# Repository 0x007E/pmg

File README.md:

# `PMG` - Audio Level Meter (Pegelmessgerät)

The `pmg` project is based on a pcb with an elektret microphone signal transistor (`BC547`) amplifier and a transistor stage for level signalization.

| Experience | Level |
|:------------|:-----:|
| Soldering   |  |
| Mechanical  |  |

# Downloads

| Type      | File               | Description              |
|:---------:|:------------------:|:-------------------------|
| Simulation | [asc](https://github.com/0x007E/pmg/raw/refs/heads/main/PMG.asc) | LTSpice Simulation | 
| Lochmaster | [lm4](https://github.com/0x007E/pmg/raw/refs/heads/main/PMG.LM4) | Stripe grid circuit board | 
| Schematic | [pdf](https://github.com/0x007E/pmg/releases/latest/download/schematic.pdf) / [cadlab](https://cadlab.io/project/28569/main/files)     | Schematic files          |
| Board     | [pdf](https://github.com/0x007E/pmg/releases/latest/download/pcb.pdf) / [cadlab](https://cadlab.io/project/28569/main/files)     | Board file               |
| Drill     | [pdf](https://github.com/0x007E/pmg/releases/latest/download/drill.pdf) | Drill file               |
| BoM | [xlsx](https://github.com/0x007E/pmg/releases/latest/download/bom.xlsx) / [html](https://github.com/0x007E/pmg/releases/latest/download/bom.html) | Bill of Material as Excel/interactive HTML |
| PCB    | [zip](https://github.com/0x007E/pmg/releases/latest/download/kicad.zip) / [tar](https://github.com/0x007E/pmg/releases/latest/download/kicad.tar.gz)                | KiCAD/Gerber/BoM/Drill files       |
| Mechanical | [zip](https://github.com/0x007E/pmg/releases/latest/download/freecad.zip) / [tar](https://github.com/0x007E/pmg/releases/latest/download/freecad.tar.gz) | FreeCAD/Housing and PCB (STEP/STL) files     |

# Hardware

There are two parts of the hardware. The pcb and the housing of the `PMG`. The pcb is created with `KiCAD` and the housing with `FreeCAD`. All files are built with `github actions` so that they are ready for a production environment. The housing is printed with a 3D-printer (`Dremel 3D40`).

## PCB

The circuit board is populated on one side (Top). The best way for soldering is within a standard soldering system.

### Top Layer

### Bottom Layer

## Mechanical

The housing has a tolerance of `0.2mm` on each side of the case. So the pcb should fit perfectly in the housing. The tolerance can be modified with `FreeCAD` in the `Parameter` Spreadsheet.

### Assembled

#### Exploded

# Additional Information

| Type       | Link               | Description              |
|:----------:|:------------------:|:-------------------------|
| BC547 | [pdf](https://www.sparkfun.com/datasheets/Components/BC546.pdf) | NPN Transistor |

---

R. GAECHTER

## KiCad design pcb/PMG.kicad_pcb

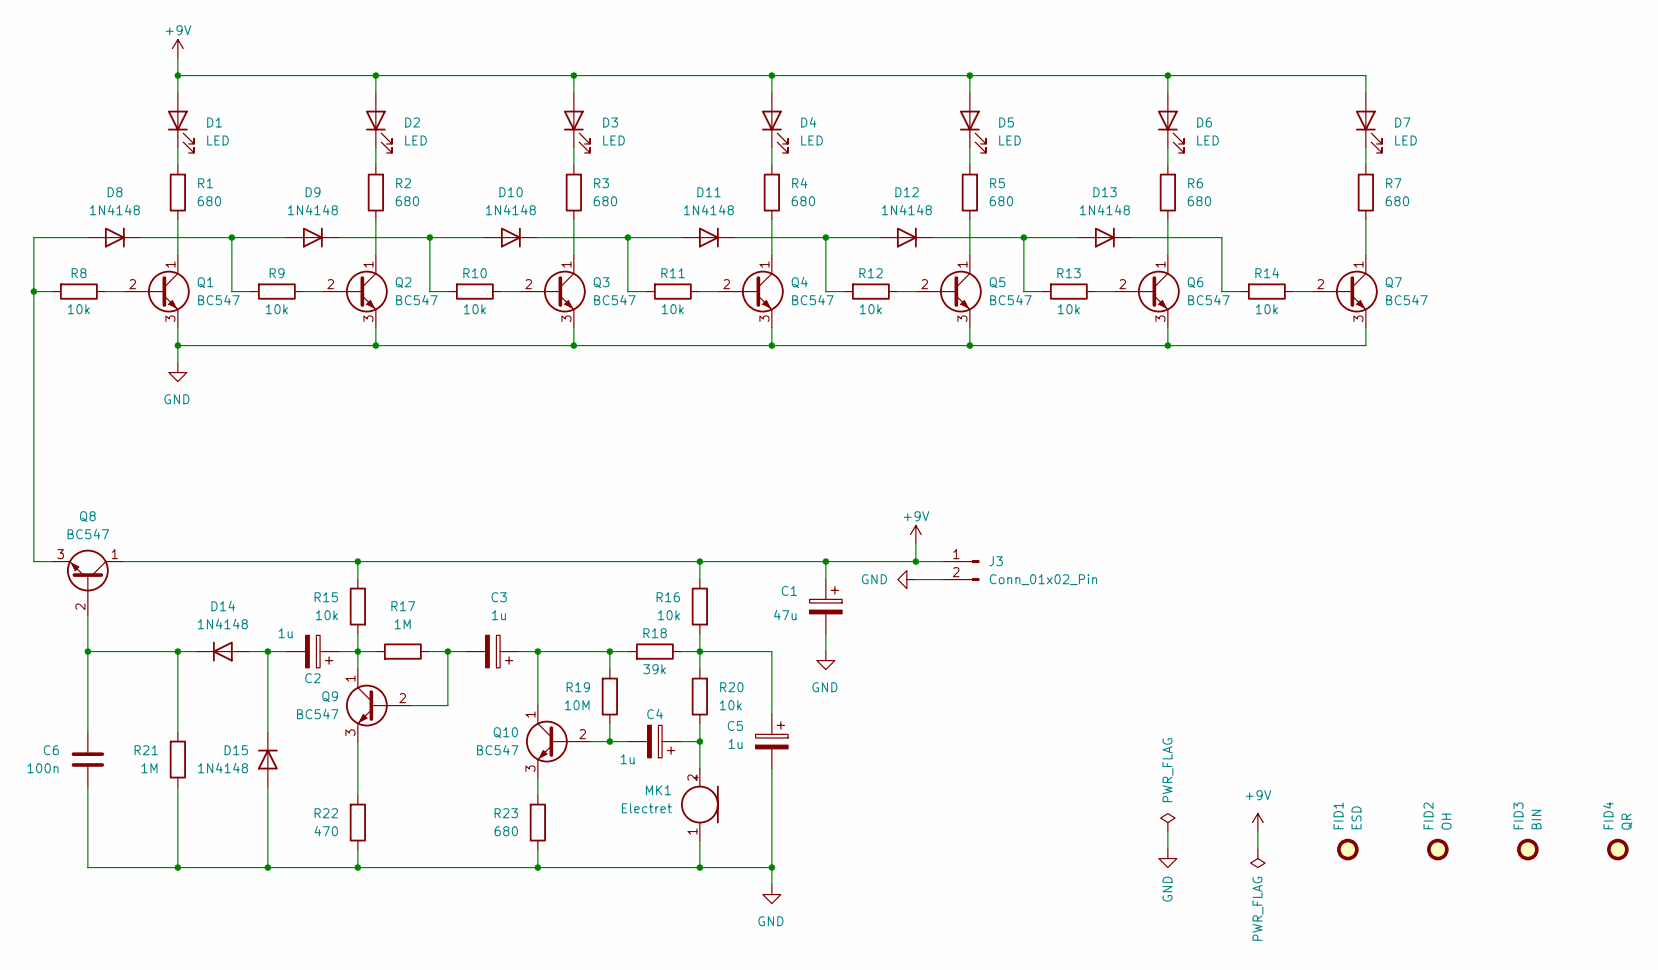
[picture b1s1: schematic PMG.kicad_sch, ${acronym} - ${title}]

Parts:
C1: 47u; CP_Radial_D5.0mm_P2.50mm
C2, C3, C4, C5: 1u; CP_Radial_D5.0mm_P2.50mm
C6: 100n; C_Disc_D5.0mm_W2.5mm_P2.50mm
D1, D2, D3, D4, D5, D6, D7: LED; LED_D5.0mm
D8, D9, D10, D11, D12, D13, D14, D15: 1N4148; D_A-405_P7.62mm_Horizontal
FID1: ESD; ESD-Logo_6.6x6mm_SilkScreen
FID2: OH; OSHW-Logo2_7.3x6mm_SilkScreen
FID3: BIN; WEEE-Logo_4.2x6mm_SilkScreen
FID4: QR; QR_0x007e_small
J3: Conn_01x02_Pin; PinHeader_1x02_P2.54mm_Vertical
MK1: Electret; Electret_THT
Q1, Q2, Q3, Q4, Q5, Q6, Q7, Q8, Q9, Q10: BC547; TO-92_Wide
R1, R2, R3, R4, R5, R6, R7, R23: 680; R_Axial_DIN0207_L6.3mm_D2.5mm_P10.16mm_Horizontal
R8, R9, R10, R11, R12, R13, R14, R15, R16, R20: 10k; R_Axial_DIN0207_L6.3mm_D2.5mm_P10.16mm_Horizontal
R17, R21: 1M; R_Axial_DIN0207_L6.3mm_D2.5mm_P10.16mm_Horizontal
R18: 39k; R_Axial_DIN0207_L6.3mm_D2.5mm_P10.16mm_Horizontal
R19: 10M; R_Axial_DIN0207_L6.3mm_D2.5mm_P10.16mm_Horizontal
R22: 470; R_Axial_DIN0207_L6.3mm_D2.5mm_P10.16mm_Horizontal

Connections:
+9V: C1.1, D1.2 (A), D2.2 (A), D3.2 (A), D4.2 (A), D5.2 (A), D6.2 (A), D7.2 (A), J3.1, Q8.1 (C), R15.1, R16.1
GND: C1.2, C5.2, C6.2, D15.2 (A), J3.2, MK1.1 (-), Q1.3 (E), Q2.3 (E), Q3.3 (E), Q4.3 (E), Q5.3 (E), Q6.3 (E), Q7.3 (E), R21.1, R22.1, R23.1
unnamed: C5.1, R16.2, R18.1, R20.2
unnamed: D1.1 (K), R1.2
unnamed: D2.1 (K), R2.2
unnamed: D3.1 (K), R3.2
unnamed: D4.1 (K), R4.2
unnamed: D5.1 (K), R5.2
unnamed: D6.1 (K), R6.2
unnamed: D7.1 (K), R7.2
unnamed: D8.2 (A), Q8.3 (E), R8.2
unnamed: D8.1 (K), D9.2 (A), R9.2
unnamed: D9.1 (K), D10.2 (A), R10.2
unnamed: D10.1 (K), D11.2 (A), R11.2
unnamed: D11.1 (K), D12.2 (A), R12.2
unnamed: D12.1 (K), D13.2 (A), R13.2
unnamed: D13.1 (K), R14.2
unnamed: C2.2, D14.2 (A), D15.1 (K)
unnamed: C6.1, D14.1 (K), Q8.2 (B), R21.2
unnamed: C4.1, MK1.2 (+), R20.1
unnamed: Q1.2 (B), R8.1
unnamed: Q1.1 (C), R1.1
unnamed: Q2.2 (B), R9.1
unnamed: Q2.1 (C), R2.1
unnamed: Q3.2 (B), R10.1
unnamed: Q3.1 (C), R3.1
unnamed: Q4.2 (B), R11.1
unnamed: Q4.1 (C), R4.1
unnamed: Q5.2 (B), R12.1
unnamed: Q5.1 (C), R5.1
unnamed: Q6.2 (B), R13.1
unnamed: Q6.1 (C), R6.1
unnamed: Q7.2 (B), R14.1
unnamed: Q7.1 (C), R7.1
unnamed: C3.2, Q9.2 (B), R17.1
unnamed: C2.1, Q9.1 (C), R15.2, R17.2
unnamed: Q9.3 (E), R22.2
unnamed: C4.2, Q10.2 (B), R19.1
unnamed: C3.1, Q10.1 (C), R18.2, R19.2
unnamed: Q10.3 (E), R23.2

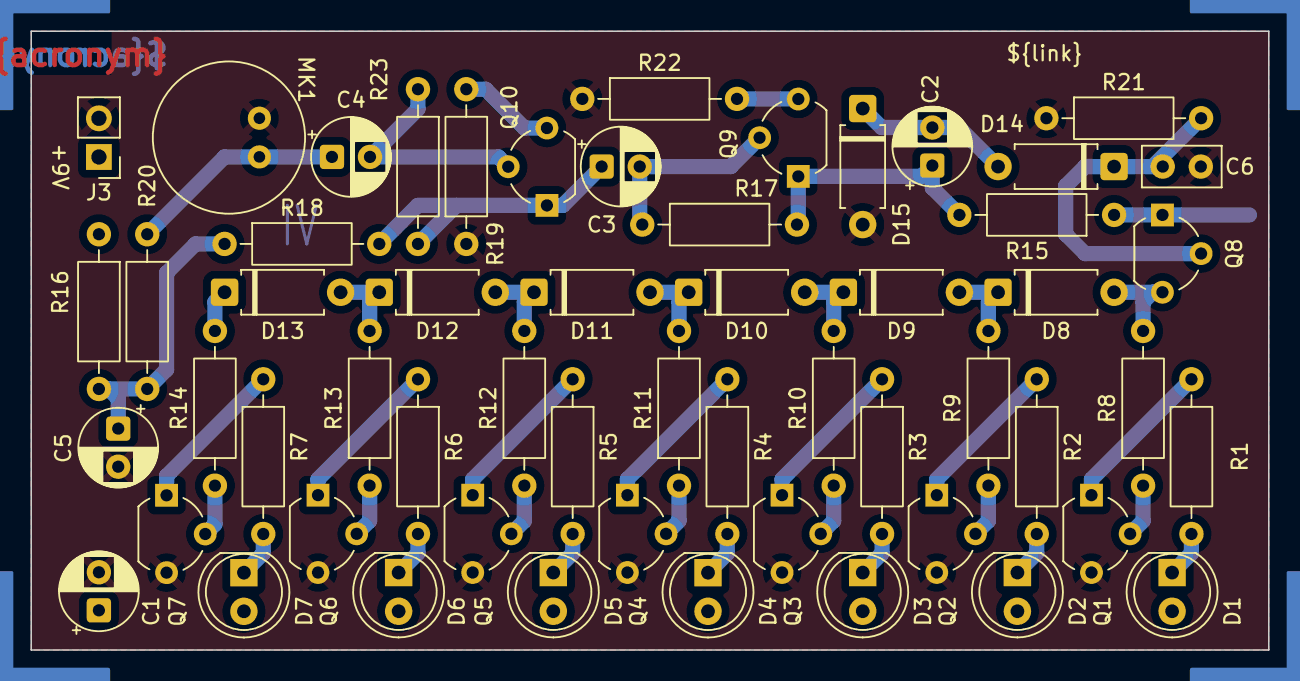
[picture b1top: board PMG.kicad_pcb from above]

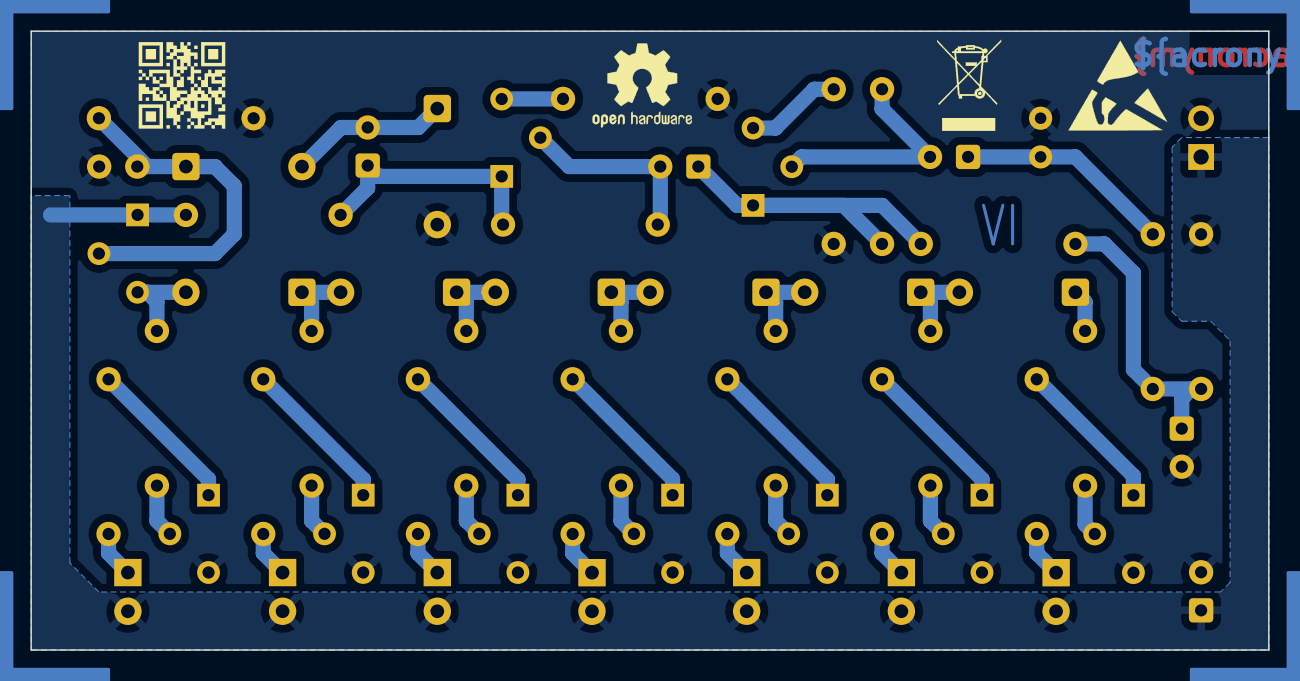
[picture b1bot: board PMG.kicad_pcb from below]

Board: 2 copper layers, 81.3 x 40.6 mm, 60 parts (4 on the bottom side), 40 nets.

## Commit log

2024-10-15 Fix README
2024-10-15 Revert "Fix README"
2024-10-15 Revert "Revert "Fix README""
    This reverts commit 95ae36aa36ba77b11c905d96ecaf28e4752392bb.
2024-10-16 Fix CADLAB link
2024-10-18 Fix typo
2026-05-26 Update to KiCAD 9
2026-05-26 Text smoothing
2026-05-26 Optimize/Extend build pipeline
2026-05-26 Rename/Remove bom fields
2026-05-26 Optimize/Extend release pipeline

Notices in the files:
README.md:
License CC By-NC-SA
parts and their libraries:
license: CC BY-NC-SA 4.0
